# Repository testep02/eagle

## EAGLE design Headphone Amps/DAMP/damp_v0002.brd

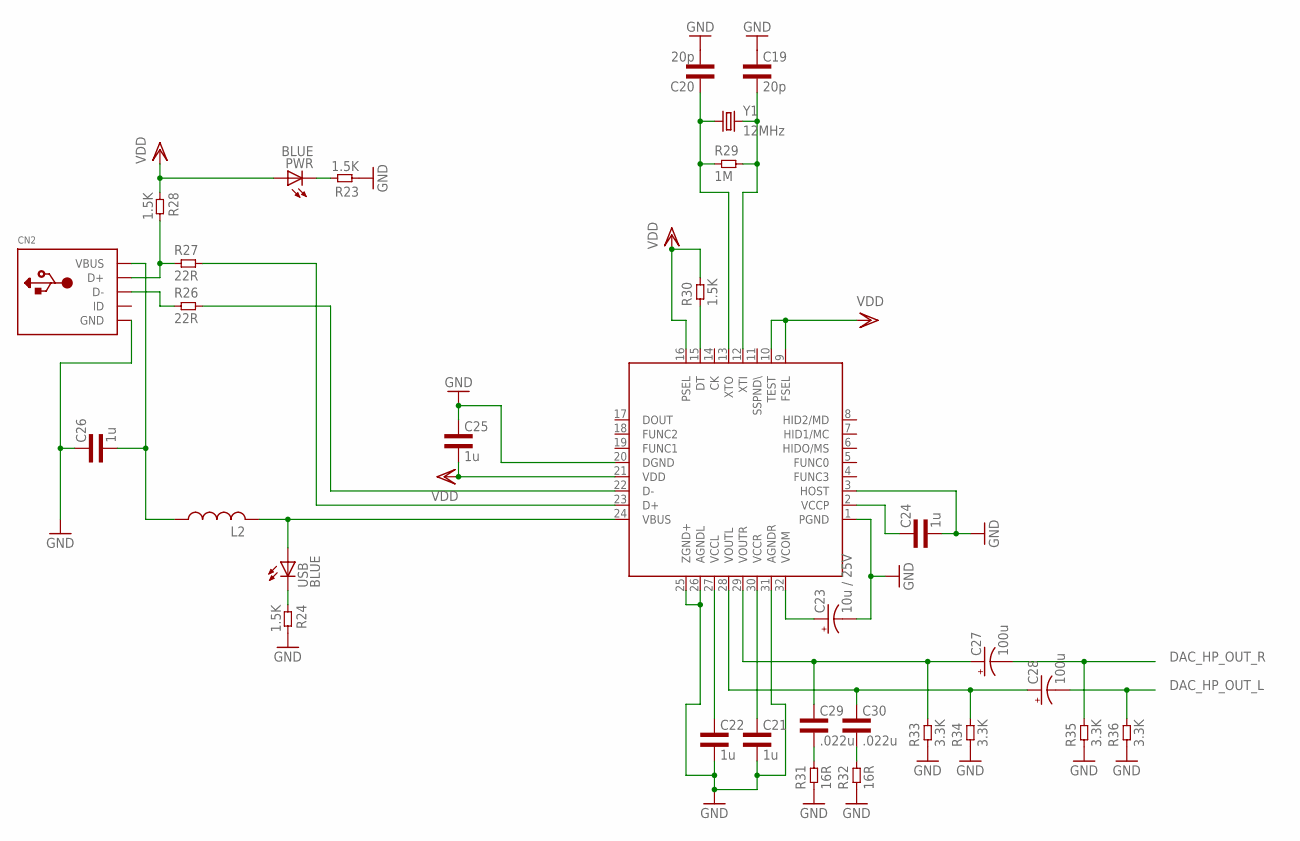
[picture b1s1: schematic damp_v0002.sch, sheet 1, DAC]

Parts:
C19, C20: 20p; 0603L3
C21, C22, C24, C25, C26: 1u; 0603L3
C23: 10u / 25V; E1,8-4
C27, C28: 100u; E2-5
C29, C30: .022u; 0603L3
CN2: USBMINIB; USB-MINIB
L2: RCL_L-USL3225M; RCL_L3225M
PWR: BLUE; LED-0603
R23, R24, R28, R30: 1.5K; 0603L3
R26, R27: 22R; 0603L3
R29: 1M; 0603L3
R31, R32: 16R; 0603L3
R33, R34, R35, R36: 3.3K; 0603L3
U$1: PCM2707_V1_PCM2704C_PCM2707
USB: BLUE; LED-0603
Y1: 12MHz; HC49US

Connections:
DAC_HP_OUT_L: C28.-, R36.P$2 (2); also elsewhere on the board
DAC_HP_OUT_R: C27.-, R35.P$2 (2); also elsewhere on the board
GND: C19.P$1 (1), C20.P$2 (2), C21.P$2 (2), C22.P$2 (2), C23.-, C24.P$2 (2), C25.P$1 (1), C26.P$1 (1), CN2.GND, R23.P$1 (1), R24.P$2 (2), R31.P$1 (1), R32.P$1 (1), R33.P$1 (1), R34.P$1 (1), R35.P$1 (1), R36.P$1 (1), U$1.1 (PGND), U$1.3 (HOST), U$1.20 (DGND), U$1.25 (ZGND+), U$1.26 (AGNDL), U$1.31 (AGNDR); also elsewhere on the board
unnamed: PWR.C, R23.P$2 (2)
unnamed: R24.P$1 (1), USB.C
unnamed: CN2.D+, R27.P$1 (1), R28.P$2 (2)
unnamed: CN2.D-, R26.P$1 (1)
unnamed: R27.P$2 (2), U$1.23 (D+)
unnamed: R26.P$2 (2), U$1.22 (D-)
unnamed: C20.P$1 (1), R29.P$1 (1), U$1.13 (XTO), Y1.1
unnamed: C19.P$2 (2), R29.P$2 (2), U$1.12 (XTI), Y1.2
unnamed: C22.P$1 (1), U$1.27 (VCCL)
unnamed: C21.P$1 (1), U$1.30 (VCCR)
unnamed: C23.+, U$1.32 (VCOM)
unnamed: C29.P$2 (2), R31.P$2 (2)
unnamed: C24.P$1 (1), U$1.2 (VCCP)
unnamed: C27.+, C29.P$1 (1), R33.P$2 (2), U$1.29 (VOUTR)
unnamed: L2.2, U$1.24 (VBUS), USB.A
unnamed: C26.P$2 (2), CN2.VBUS, L2.1
unnamed: C28.+, C30.P$1 (1), R34.P$2 (2), U$1.28 (VOUTL)
unnamed: R30.P$1 (1), U$1.15 (DT)
unnamed: C30.P$2 (2), R32.P$2 (2)
VDD: C25.P$2 (2), PWR.A, R28.P$1 (1), R30.P$2 (2), U$1.9 (FSEL), U$1.10 (TEST), U$1.16 (PSEL), U$1.21 (VDD)

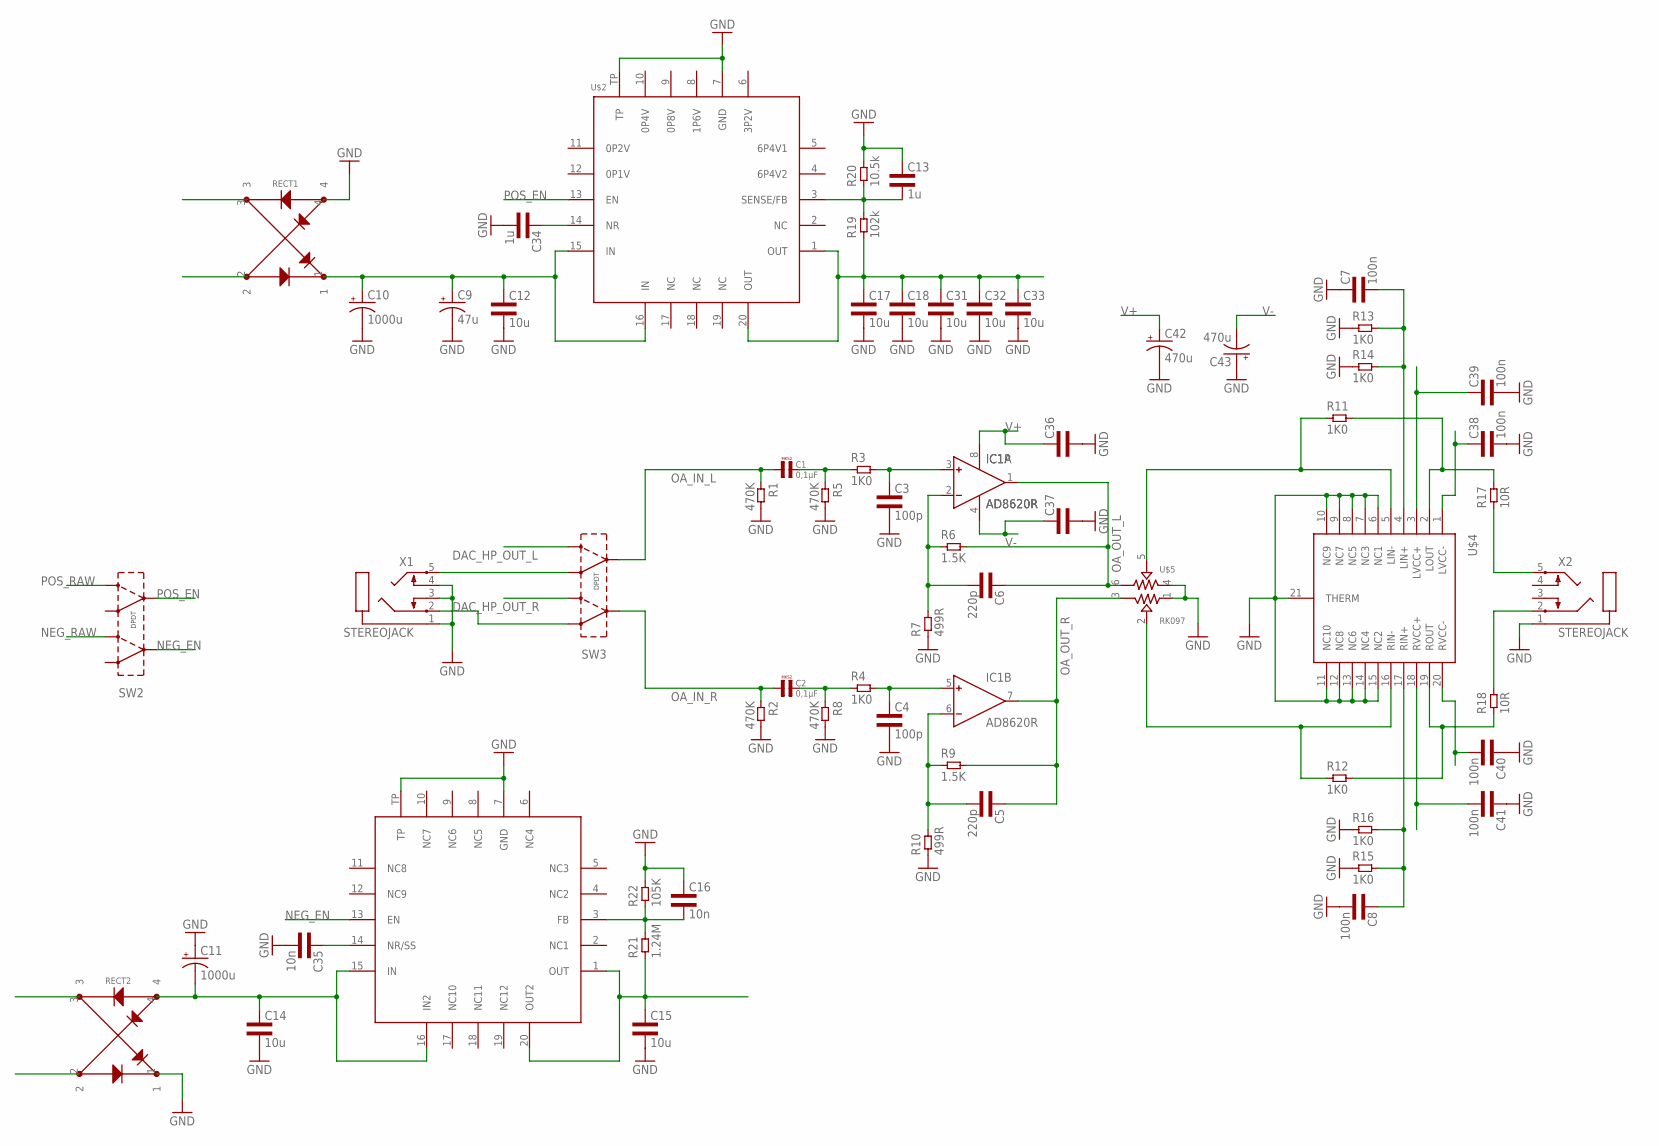
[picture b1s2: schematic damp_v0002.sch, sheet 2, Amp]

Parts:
C1, C2: 0,1µF; R5B2K5
C3, C4: 100p; 0603L3
C5, C6: 220p; 0603L3
C7, C8, C38, C39, C40, C41: 100n; 0603L3
C9: 47u; CT7343
C10, C11: 1000u; E7,5-16
C12, C14, C15, C17, C18, C31, C32, C33: 10u; 0805L3
C13, C34: 1u; 0603L3
C16, C35: 10n; 0603L3
C36, C37: CAP0603L3; 0603L3
C42, C43: 470u; E5-10,5
IC1: AD8620R; SO8
R1, R2, R5, R8: 470K; 0603L3
R3, R4, R11, R12, R13, R14, R15, R16: 1K0; 0603L3
R6, R9: 1.5K; 0603L3
R7, R10: 499R; 0603L3
R17, R18: 10R; 1206L3
R19: 102k; 0603L3
R20: 10.5k; 0603L3
R21: 1.24M; 0603L3
R22: 105K; 0603L3
RECT1, RECT2: RECTIFIER_Z4GP206; RECTIFIER_ABS-4
SW2, SW3: DPDTCAS-A; CAS-A
U$2: POWER-SUPPLY_POS_V1_TI_LDO_TPS7A4700; POWER-SUPPLY_POS_V1_TI_LDO_VQFN-20
U$3: POWER-SUPPLY_POS_V1_TI_LDO_TPS7A3301RGWT; POWER-SUPPLY_POS_V1_TI_LDO_VQFN-20
U$4: PCM2707_V1_AMP_TPA6120_TPA6120
U$5: RK097
X1, X2: STEREOJACK; STX3100

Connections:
AC1: RECT1.3
AC2: RECT1.2
AC3: RECT2.3
AC4: RECT2.2
DAC_HP_OUT_L: SW3.P$6 (OUTB2); also elsewhere on the board
DAC_HP_OUT_R: SW3.P$3 (OUTA2); also elsewhere on the board
GND: C3.P$2 (2), C4.P$2 (2), C7.P$1 (1), C8.P$2 (2), C9.-, C10.-, C11.+, C12.2, C13.P$1 (1), C14.2, C15.2, C16.P$1 (1), C17.2, C18.2, C31.2, C32.2, C33.2, C34.P$2 (2), C35.P$2 (2), C36.P$2 (2), C37.P$2 (2), C38.P$2 (2), C39.P$2 (2), C40.P$1 (1), C41.P$1 (1), C42.-, C43.+, R1.P$2 (2), R2.P$2 (2), R5.P$2 (2), R7.P$1 (1), R8.P$2 (2), R10.P$1 (1), R13.P$1 (1), R14.P$1 (1), R15.P$1 (1), R16.P$1 (1), R20.P$2 (2), R22.P$2 (2), RECT1.4, RECT2.1, U$2.7 (GND), U$2.TP, U$3.7 (GND), U$3.TP, U$4.6 (NC1), U$4.7 (NC3), U$4.8 (NC5), U$4.9 (NC7), U$4.10 (NC9), U$4.11 (NC10), U$4.12 (NC8), U$4.13 (NC6), U$4.14 (NC4), U$4.15 (NC2), U$4.21 (THERM), U$5.1, U$5.4, X1.1, X1.3, X1.4, X2.1; also elsewhere on the board
unnamed: SW3.P$4 (OUTB1), X1.5
unnamed: SW3.P$1 (OUTA1), X1.2
unnamed: C34.P$1 (1), U$2.14 (NR)
unnamed: C1.2, R3.P$1 (1), R5.P$1 (1)
unnamed: C3.P$1 (1), IC1.3 (IN+), R3.P$2 (2)
unnamed: C6.P$2 (2), IC1.2 (IN-), R6.P$1 (1), R7.P$2 (2)
unnamed: R11.P$1 (1), U$4.5 (LIN-), U$5.5
unnamed: R12.P$1 (1), U$4.16 (RIN-), U$5.2
unnamed: C2.2, R4.P$1 (1), R8.P$1 (1)
unnamed: C4.P$1 (1), IC1.5 (IN+), R4.P$2 (2)
unnamed: R11.P$2 (2), R17.2, U$4.2 (LOUT)
unnamed: C5.P$2 (2), IC1.6 (IN-), R9.P$1 (1), R10.P$2 (2)
unnamed: R12.P$2 (2), R18.1, U$4.19 (ROUT)
unnamed: C7.P$2 (2), R13.P$2 (2), R14.P$2 (2), U$4.4 (LIN+)
unnamed: C8.P$1 (1), R15.P$2 (2), R16.P$2 (2), U$4.17 (RIN+)
unnamed: R17.1, X2.5
unnamed: R18.2, X2.2
unnamed: C13.P$2 (2), R19.P$2 (2), R20.P$1 (1), U$2.3 (SENSE/FB)
unnamed: C16.P$2 (2), R21.P$2 (2), R22.P$1 (1), U$3.3 (FB)
unnamed: C35.P$1 (1), U$3.14 (NR/SS)
NEG_EN: SW2.P$2 (INA), U$3.13 (EN)
NEG_RAW: C11.-, C14.1, RECT2.4, SW2.P$3 (OUTA2), U$3.15 (IN), U$3.16 (IN2)
OA_IN_L: C1.1, R1.P$1 (1), SW3.P$5 (INB)
OA_IN_R: C2.1, R2.P$1 (1), SW3.P$2 (INA)
OA_OUT_L: C6.P$1 (1), IC1.1 (OUT), R6.P$2 (2), U$5.6
OA_OUT_R: C5.P$1 (1), IC1.7 (OUT), R9.P$2 (2), U$5.3
POS_EN: SW2.P$5 (INB), U$2.13 (EN)
POS_RAW: C9.+, C10.+, C12.1, RECT1.1, SW2.P$6 (OUTB2), U$2.15 (IN), U$2.16 (IN)
V+: C17.1, C18.1, C31.1, C32.1, C33.1, C36.P$1 (1), C39.P$1 (1), C41.P$2 (2), C42.+, IC1.8 (V+), R19.P$1 (1), U$2.1 (OUT), U$2.20 (OUT), U$4.3 (LVCC+), U$4.18 (RVCC+)
V-: C15.1, C37.P$1 (1), C38.P$1 (1), C40.P$2 (2), C43.-, IC1.4 (V-), R21.P$1 (1), U$3.1 (OUT), U$3.20 (OUT2), U$4.1 (LVCC-), U$4.20 (RVCC-)

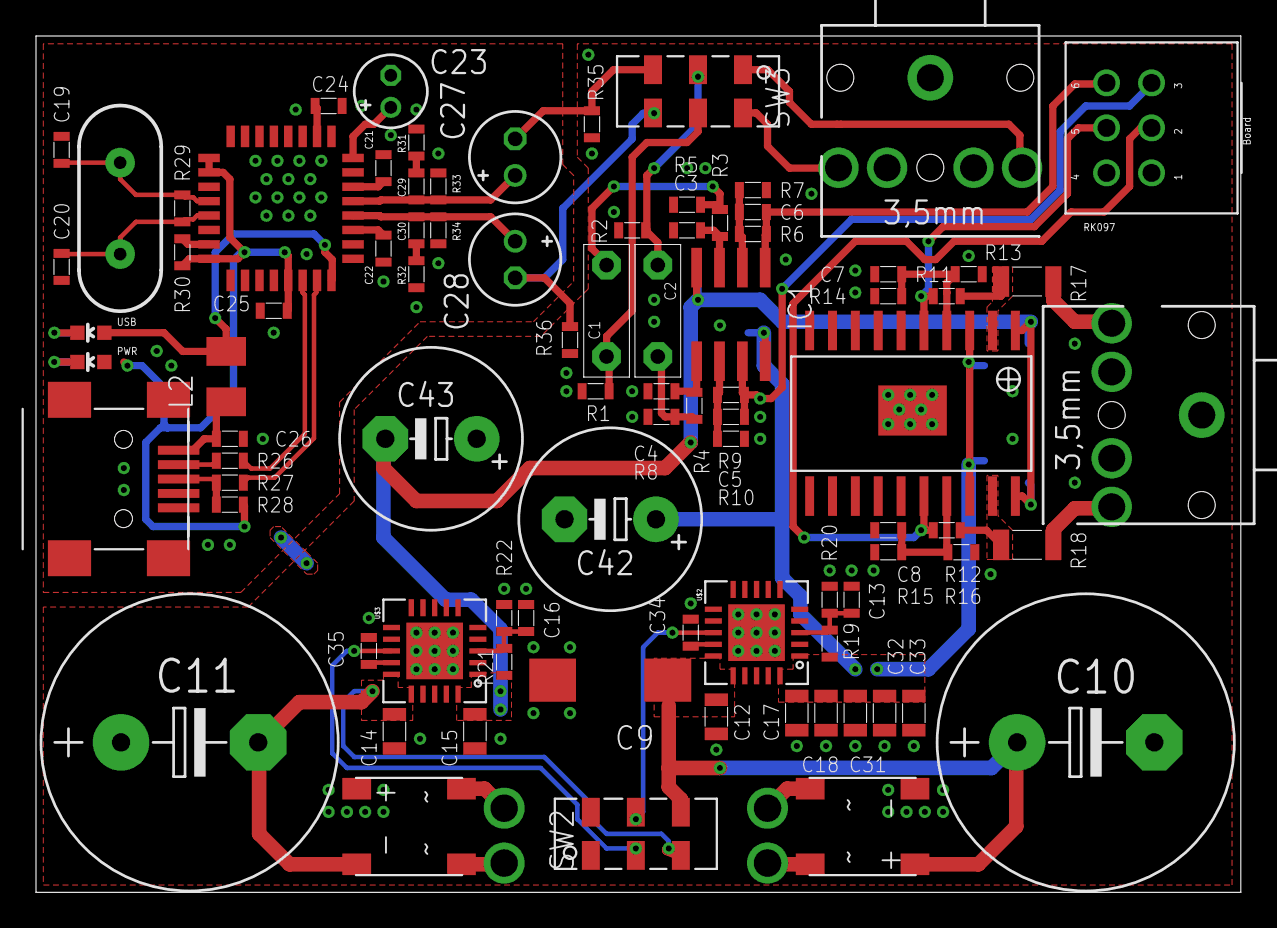
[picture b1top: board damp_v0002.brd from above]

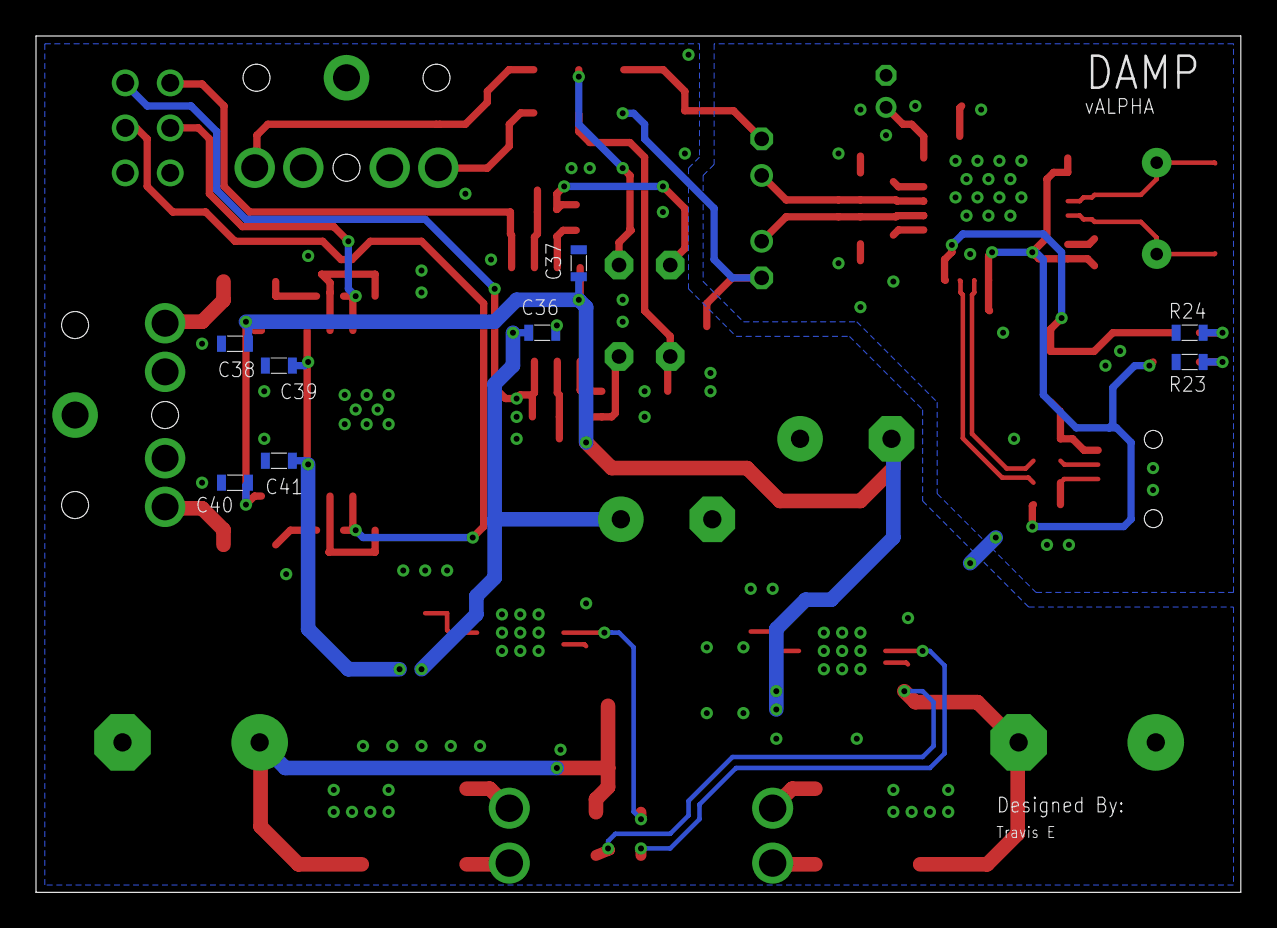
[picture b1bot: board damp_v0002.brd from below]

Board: 2 copper layers, 66.9 x 47.6 mm, 95 parts (8 on the bottom side), 53 nets.

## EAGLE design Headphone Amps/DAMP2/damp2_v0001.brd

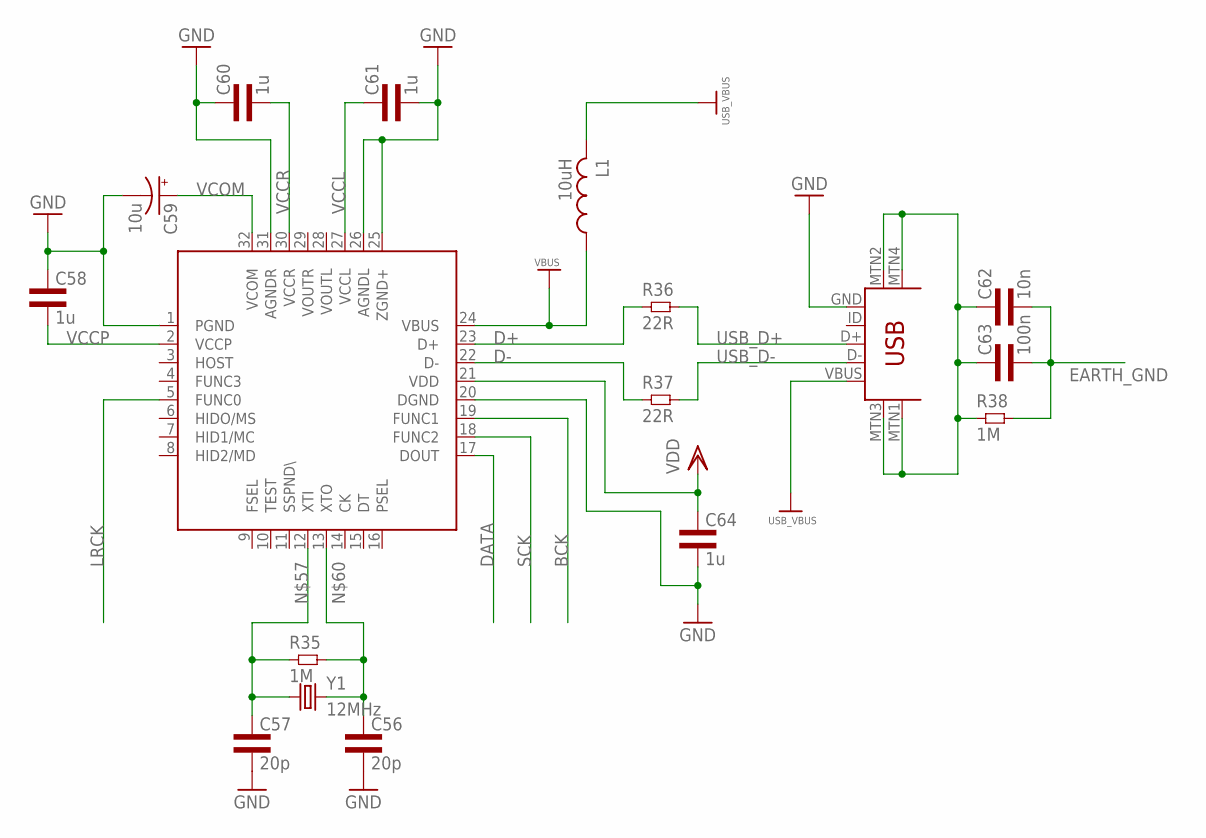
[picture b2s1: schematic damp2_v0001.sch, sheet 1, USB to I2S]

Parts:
C56, C57: 20p; 0603L3
C58, C60, C61, C64: 1u; 0603L3
C59: 10u; E1,8-4
C62: 10n; 0603L3
C63: 100n; 0603L3
L1: 10uH; L3225M
R35, R38: 1M; 0603L3
R36, R37: 22R; 0603L3
U$1: PCM2707_V1_PCM2704C_PCM2707
U$9: USB-MINIB-5PIN; USB-MINIB
Y1: 12MHz; HC49US

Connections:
BCK: U$1.19 (FUNC1); also elsewhere on the board
D+: R36.P$1 (1), U$1.23 (D+)
D-: R37.P$1 (1), U$1.22 (D-)
DATA: U$1.17 (DOUT); also elsewhere on the board
EARTH_GND: C62.P$2 (2), C63.P$2 (2), R38.P$2 (2)
GND: C56.P$2 (2), C57.P$2 (2), C58.P$1 (1), C59.-, C60.P$1 (1), C61.P$2 (2), C64.P$2 (2), U$1.1 (PGND), U$1.20 (DGND), U$1.25 (ZGND+), U$1.26 (AGNDL), U$1.31 (AGNDR), U$9.GND; also elsewhere on the board
LRCK: U$1.5 (FUNC0); also elsewhere on the board
unnamed: C57.P$1 (1), R35.P$1 (1), U$1.12 (XTI), Y1.1
unnamed: C56.P$1 (1), R35.P$2 (2), U$1.13 (XTO), Y1.2
unnamed: C62.P$1 (1), C63.P$1 (1), R38.P$1 (1), U$9.MTN1 (MTN2), U$9.MTN2 (MTN3), U$9.MTN3 (MTN1), U$9.MTN4
SCK: U$1.18 (FUNC2); also elsewhere on the board
USB_D+: R36.P$2 (2), U$9.D+
USB_D-: R37.P$2 (2), U$9.D-
USB_VBUS: L1.2, U$9.VBUS
VBUS: L1.1, U$1.24 (VBUS)
VCCL: C61.P$1 (1), U$1.27 (VCCL)
VCCP: C58.P$2 (2), U$1.2 (VCCP)
VCCR: C60.P$2 (2), U$1.30 (VCCR)
VCOM: C59.+, U$1.32 (VCOM)
VDD: C64.P$1 (1), U$1.21 (VDD)

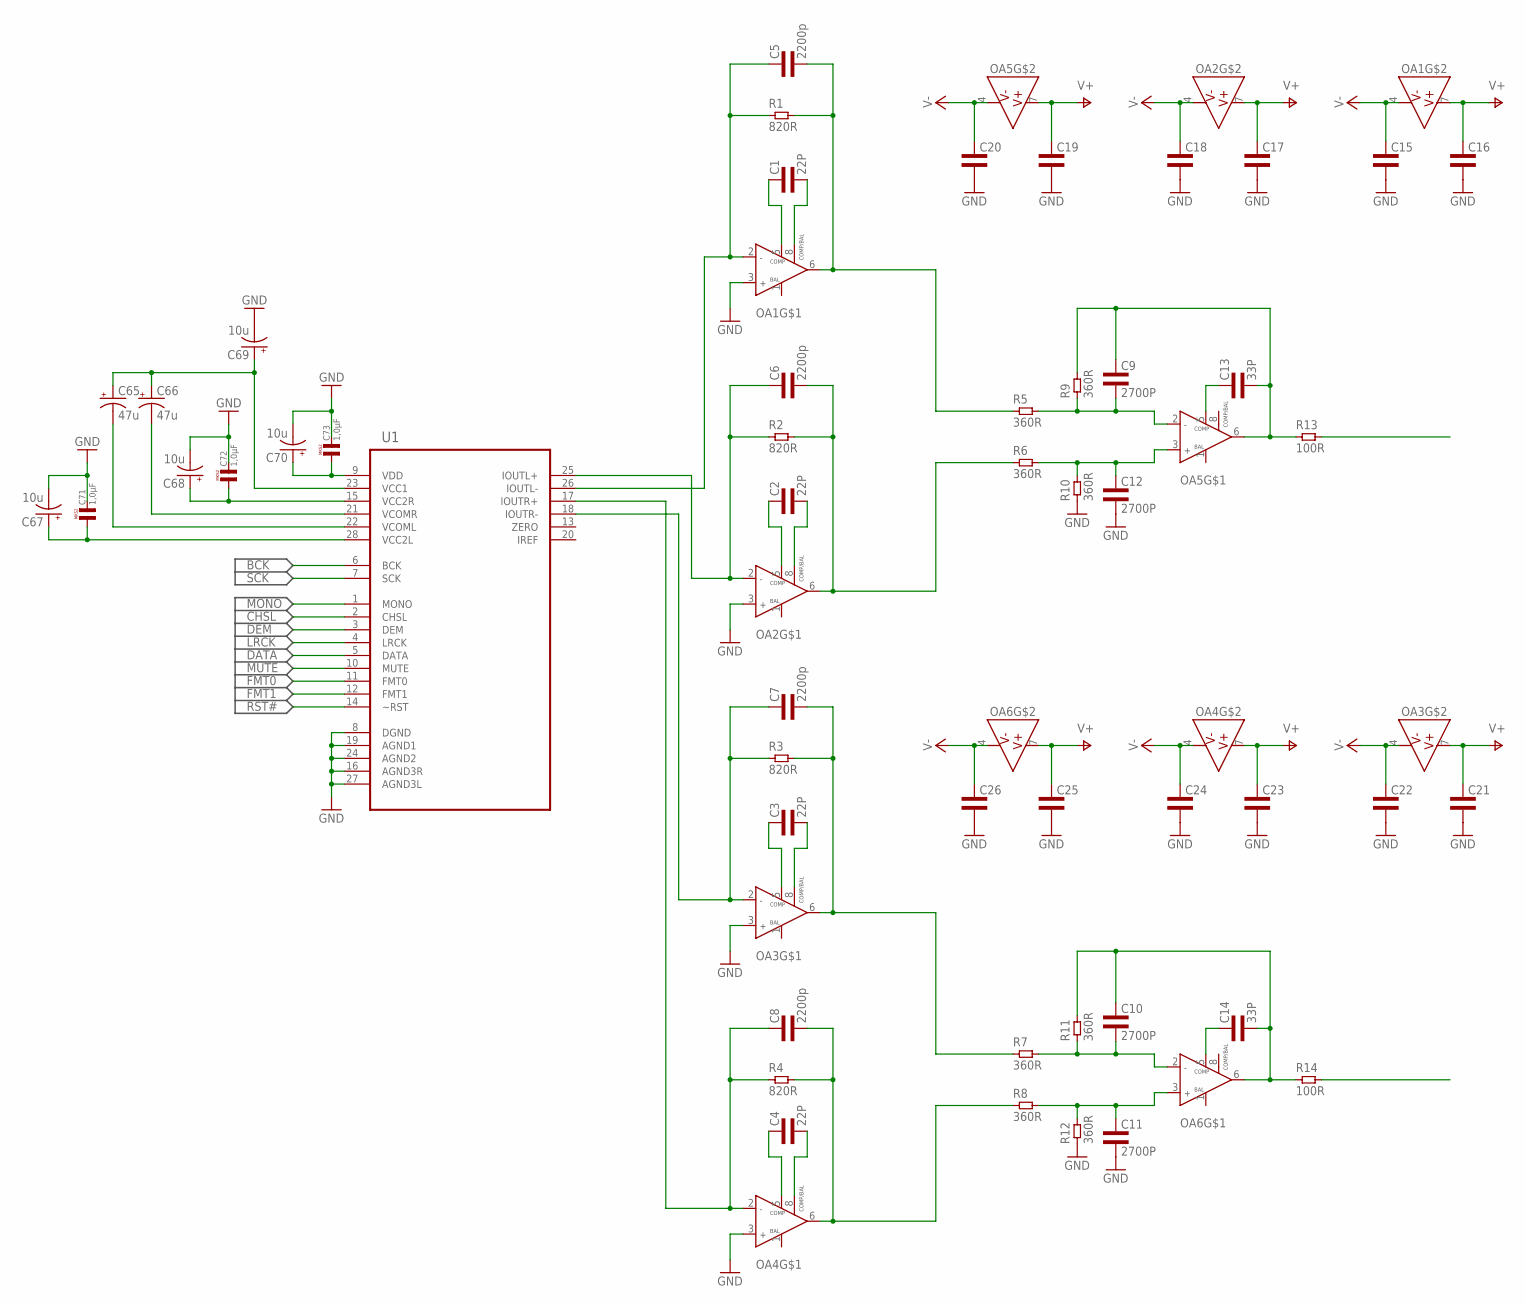
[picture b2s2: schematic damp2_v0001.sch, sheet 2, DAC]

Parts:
C1, C2, C3, C4: 22P; 0603L3
C5, C6, C7, C8: 2200p; 0603L3
C9, C10, C11, C12: 2700P; 0805L3
C13, C14: 33P; 0603L3
C15, C16, C17, C18, C19, C20, C21, C22, C23, C24, C25, C26: CAP0603L3; 0603L3
C65, C66: 47u; A/3216-18W
C67, C68, C69, C70: 10u; A/3216-18W
C71, C72, C73: 1,0µF; R5B5
OA1, OA2, OA3, OA4: NE5534DSOIC8; SOIC-8
OA5, OA6: NE5534ADSOIC8; SOIC-8
R1, R2, R3, R4: 820R; 0603L3
R5, R6, R7, R8, R9, R10, R11, R12: 360R; 0805L3
R13, R14: 100R; 0805L3
U1: TEXAS-INSTRUMENTS_BY_ELEMENT14_BATCH_1_PCM1794ADB; TEXAS-INSTRUMENTS_BY_ELEMENT14_BATCH_1_SOP65P780X200-28N

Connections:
BCK: U1.6 (BCK); also elsewhere on the board
CHSL: U1.2 (CHSL)
DATA: U1.5 (DATA); also elsewhere on the board
DEM: U1.3 (DEM)
FMT0: U1.11 (FMT0)
FMT1: U1.12 (FMT1)
GND: C11.2, C12.2, C15.P$2 (2), C16.P$2 (2), C17.P$2 (2), C18.P$2 (2), C19.P$2 (2), C20.P$2 (2), C21.P$2 (2), C22.P$2 (2), C23.P$2 (2), C24.P$2 (2), C25.P$2 (2), C26.P$2 (2), C67.-, C68.-, C69.-, C70.-, C71.2, C72.2, C73.2, OA1.3 (IN+), OA2.3 (IN+), OA3.3 (IN+), OA4.3 (IN+), R10.1, R12.1, U1.8 (DGND), U1.16 (AGND3R), U1.19 (AGND1), U1.24 (AGND2), U1.27 (AGND3L); also elsewhere on the board
LRCK: U1.4 (LRCK); also elsewhere on the board
MONO: U1.1 (MONO)
MUTE: U1.10 (MUTE)
unnamed: C1.P$1 (1), OA1.5 (COMP)
unnamed: C1.P$2 (2), OA1.8 (COMP/BAL)
unnamed: C2.P$1 (1), OA2.5 (COMP)
unnamed: C2.P$2 (2), OA2.8 (COMP/BAL)
unnamed: C3.P$1 (1), OA3.5 (COMP)
unnamed: C3.P$2 (2), OA3.8 (COMP/BAL)
unnamed: C4.P$1 (1), OA4.5 (COMP)
unnamed: C4.P$2 (2), OA4.8 (COMP/BAL)
unnamed: C5.P$1 (1), OA1.2 (IN-), R1.P$1 (1), U1.26 (IOUTL-)
unnamed: C6.P$1 (1), OA2.2 (IN-), R2.P$1 (1), U1.25 (IOUTL+)
unnamed: C7.P$1 (1), OA3.2 (IN-), R3.P$1 (1), U1.18 (IOUTR-)
unnamed: C8.P$1 (1), OA4.2 (IN-), R4.P$1 (1), U1.17 (IOUTR+)
unnamed: C6.P$2 (2), OA2.6 (OUT), R2.P$2 (2), R6.1
unnamed: C5.P$2 (2), OA1.6 (OUT), R1.P$2 (2), R5.1
unnamed: C7.P$2 (2), OA3.6 (OUT), R3.P$2 (2), R7.1
unnamed: C8.P$2 (2), OA4.6 (OUT), R4.P$2 (2), R8.1
unnamed: C10.2, OA6.2 (IN-), R7.2, R11.1
unnamed: C11.1, OA6.3 (IN+), R8.2, R12.2
unnamed: C9.2, OA5.2 (IN-), R5.2, R9.1
unnamed: C12.1, OA5.3 (IN+), R6.2, R10.2
unnamed: C13.P$1 (1), OA5.5 (COMP)
unnamed: C14.P$1 (1), OA6.5 (COMP)
unnamed: C10.1, C14.P$2 (2), OA6.6 (OUT), R11.2, R14.1
unnamed: C9.1, C13.P$2 (2), OA5.6 (OUT), R9.2, R13.1
unnamed: C70.+, C73.1, U1.9 (VDD)
unnamed: C65.+, C66.+, C69.+, U1.23 (VCC1)
unnamed: C68.+, C72.1, U1.15 (VCC2R)
unnamed: C66.-, U1.21 (VCOMR)
unnamed: C65.-, U1.22 (VCOML)
unnamed: C67.+, C71.1, U1.28 (VCC2L)
RST#: U1.14 (~RST)
SCK: U1.7 (SCK); also elsewhere on the board
V+: C16.P$1 (1), C17.P$1 (1), C19.P$1 (1), C21.P$1 (1), C23.P$1 (1), C25.P$1 (1), OA1.7 (V+), OA2.7 (V+), OA3.7 (V+), OA4.7 (V+), OA5.7 (V+), OA6.7 (V+); also elsewhere on the board
V-: C15.P$1 (1), C18.P$1 (1), C20.P$1 (1), C22.P$1 (1), C24.P$1 (1), C26.P$1 (1), OA1.4 (V-), OA2.4 (V-), OA3.4 (V-), OA4.4 (V-), OA5.4 (V-), OA6.4 (V-); also elsewhere on the board

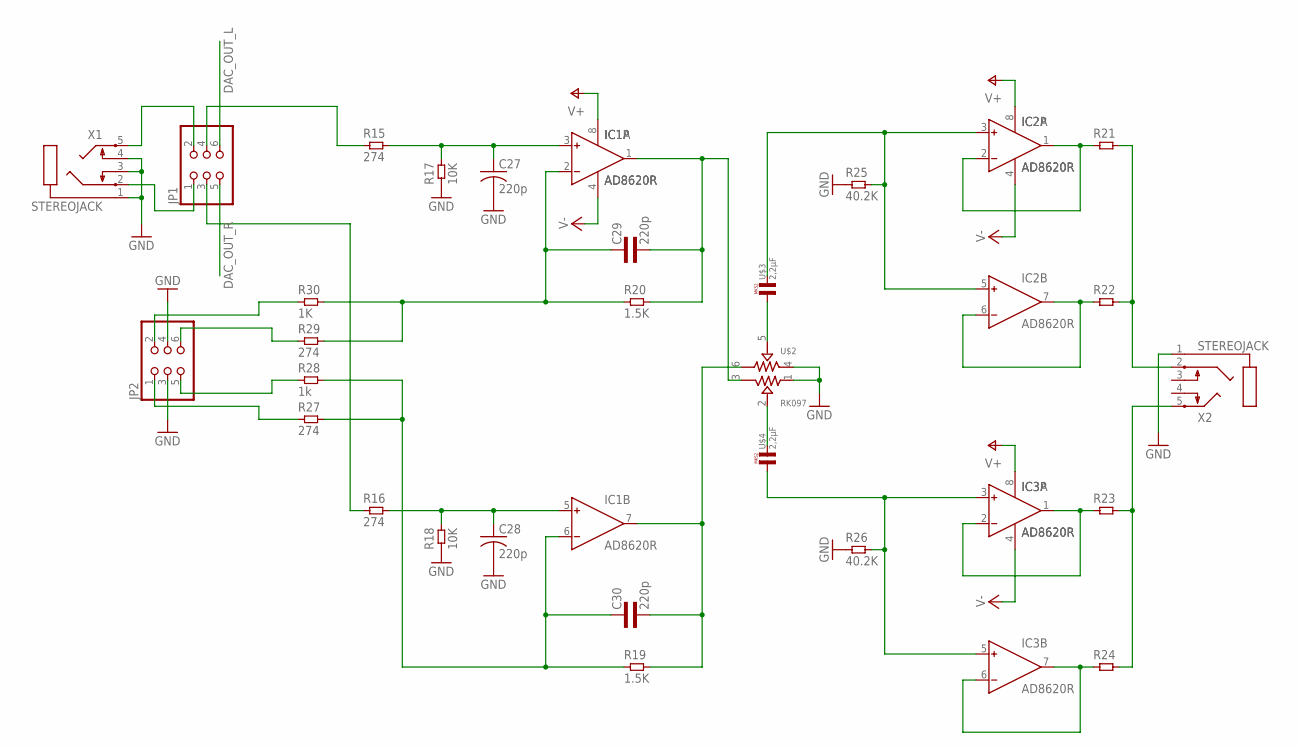
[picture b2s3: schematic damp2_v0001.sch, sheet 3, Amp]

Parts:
C27, C28: 220p; C025-025X050
C29, C30: 220p; 0805L3
IC1, IC2, IC3: AD8620R; SO8
JP1, JP2: PINHD-2X3; 2X03
R15, R16, R27, R29: 274; 0805L3
R17, R18: 10K; 0805L3
R19, R20: 1.5K; 0805L3
R21, R22, R23, R24: RES1206L3; 1206L3
R25, R26: 40.2K; 0805L3
R28: 1k; 0805L3
R30: 1K; 0805L3
U$2: RK097
U$3, U$4: 2,2µF; R5B7K2
X1, X2: STEREOJACK; STX3100

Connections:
AMP_IN_L: JP1.4, R15.1
AMP_IN_R: JP1.3, R16.1
A_IN_L: JP1.2, X1.5
A_IN_R: JP1.1, X1.2
DAC_OUT_L: JP1.6
DAC_OUT_R: JP1.5
GND: C27.2, C28.2, JP2.3, JP2.4, R17.1, R18.1, R25.1, R26.1, U$2.1, U$2.4, X1.1, X1.3, X1.4, X2.1; also elsewhere on the board
unnamed: C27.1, IC1.3 (IN+), R15.2, R17.2
unnamed: C28.1, IC1.5 (IN+), R16.2, R18.2
unnamed: C29.2, IC1.1 (OUT), R20.2, U$2.3
unnamed: C30.2, IC1.7 (OUT), R19.2, U$2.6
unnamed: C30.1, IC1.6 (IN-), R19.1, R27.2, R28.2
unnamed: C29.1, IC1.2 (IN-), R20.1, R29.2, R30.2
unnamed: U$2.2, U$4.2
unnamed: IC2.1 (OUT), IC2.2 (IN-), R21.1
unnamed: IC2.6 (IN-), IC2.7 (OUT), R22.1
unnamed: IC3.1 (OUT), IC3.2 (IN-), R23.1
unnamed: IC3.6 (IN-), IC3.7 (OUT), R24.1
unnamed: R21.2, R22.2, X2.2
unnamed: R23.2, R24.2, X2.5
unnamed: U$2.5, U$3.1
unnamed: IC3.3 (IN+), IC3.5 (IN+), R26.2, U$4.1
unnamed: IC2.3 (IN+), IC2.5 (IN+), R25.2, U$3.2
unnamed: JP2.2, R30.1
unnamed: JP2.1, R27.1
unnamed: JP2.5, R28.1
unnamed: JP2.6, R29.1
V+: IC1.8 (V+), IC2.8 (V+), IC3.8 (V+); also elsewhere on the board
V-: IC1.4 (V-), IC2.4 (V-), IC3.4 (V-); also elsewhere on the board

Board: 2 copper layers, 103 parts (2 on the bottom side), 76 nets, no tracks yet.

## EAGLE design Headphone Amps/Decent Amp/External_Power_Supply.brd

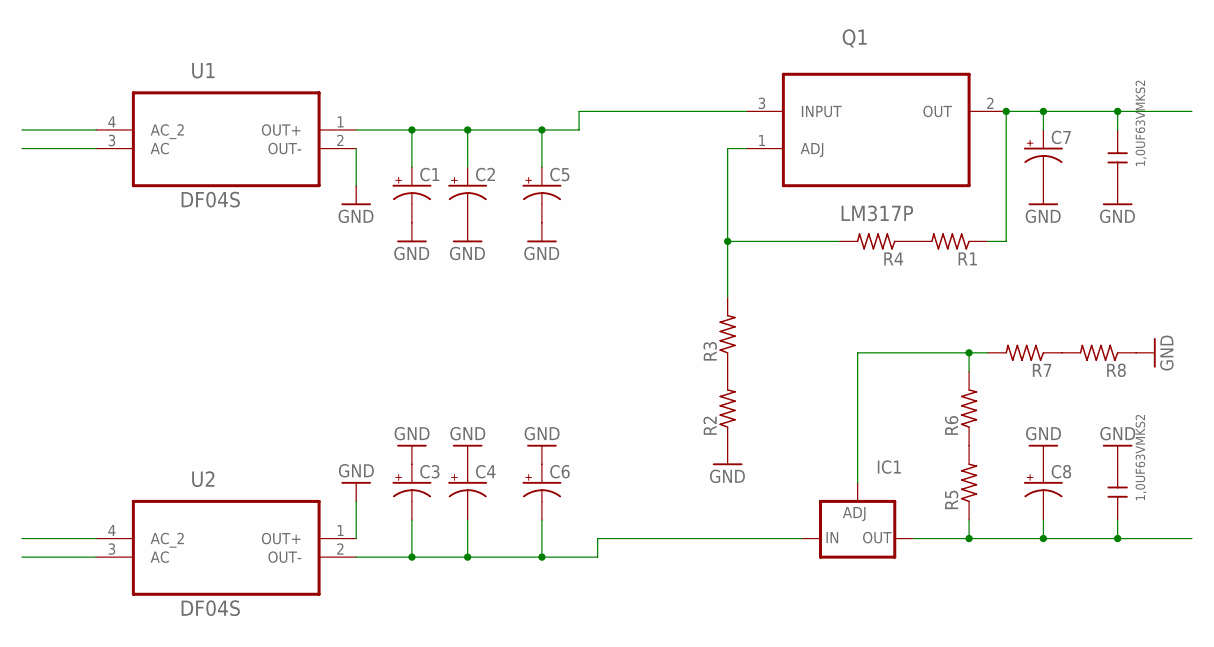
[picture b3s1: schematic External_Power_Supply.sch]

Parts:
C1, C2, C3, C4: CPOL-US153CLV-1010; 153CLV-1010
C5, C6, C7, C8: CPOL-USF; PANASONIC_F
C9, C10: 1,0UF63VMKS2; 5,0X10,0RM5,0
IC1: LM337TS; 337TS
Q1: LM317P; TO254P450X1020X2000-3P
R1, R2, R3, R4, R5, R6, R7, R8: R-US_R0603; R0603
U1, U2: DF04S; SOT508P985X260-4N

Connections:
GND: C1.-, C2.-, C3.+, C4.+, C5.-, C6.+, C7.-, C8.+, C9.1, C10.2, R2.1, R8.1, U1.2 (OUT-), U2.1 (OUT+)
unnamed: R2.2, R3.1
unnamed: C1.+, C2.+, C5.+, Q1.3 (INPUT), U1.1 (OUT+)
unnamed: C3.-, C4.-, C6.-, IC1.2 (IN), U2.2 (OUT-)
unnamed: C7.+, C9.2, Q1.2 (OUT), R1.1
unnamed: C8.-, C10.1, IC1.3 (OUT), R5.1
unnamed: Q1.1 (ADJ), R3.2, R4.2
unnamed: IC1.1 (ADJ), R6.2, R7.2
unnamed: R1.2, R4.1
unnamed: R5.2, R6.1
unnamed: R7.1, R8.2

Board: 2 copper layers, 22 parts (0 on the bottom side), 11 nets, no tracks yet.

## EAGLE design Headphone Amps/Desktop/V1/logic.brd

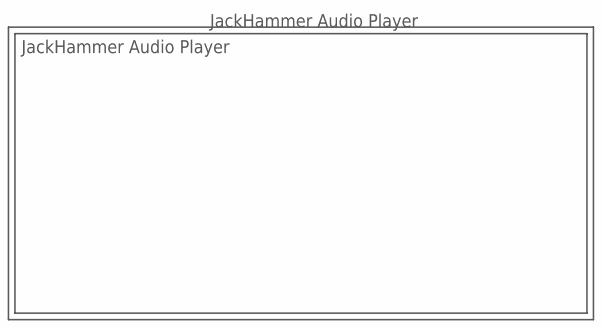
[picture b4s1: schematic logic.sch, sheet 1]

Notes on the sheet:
JackHammer Audio Player

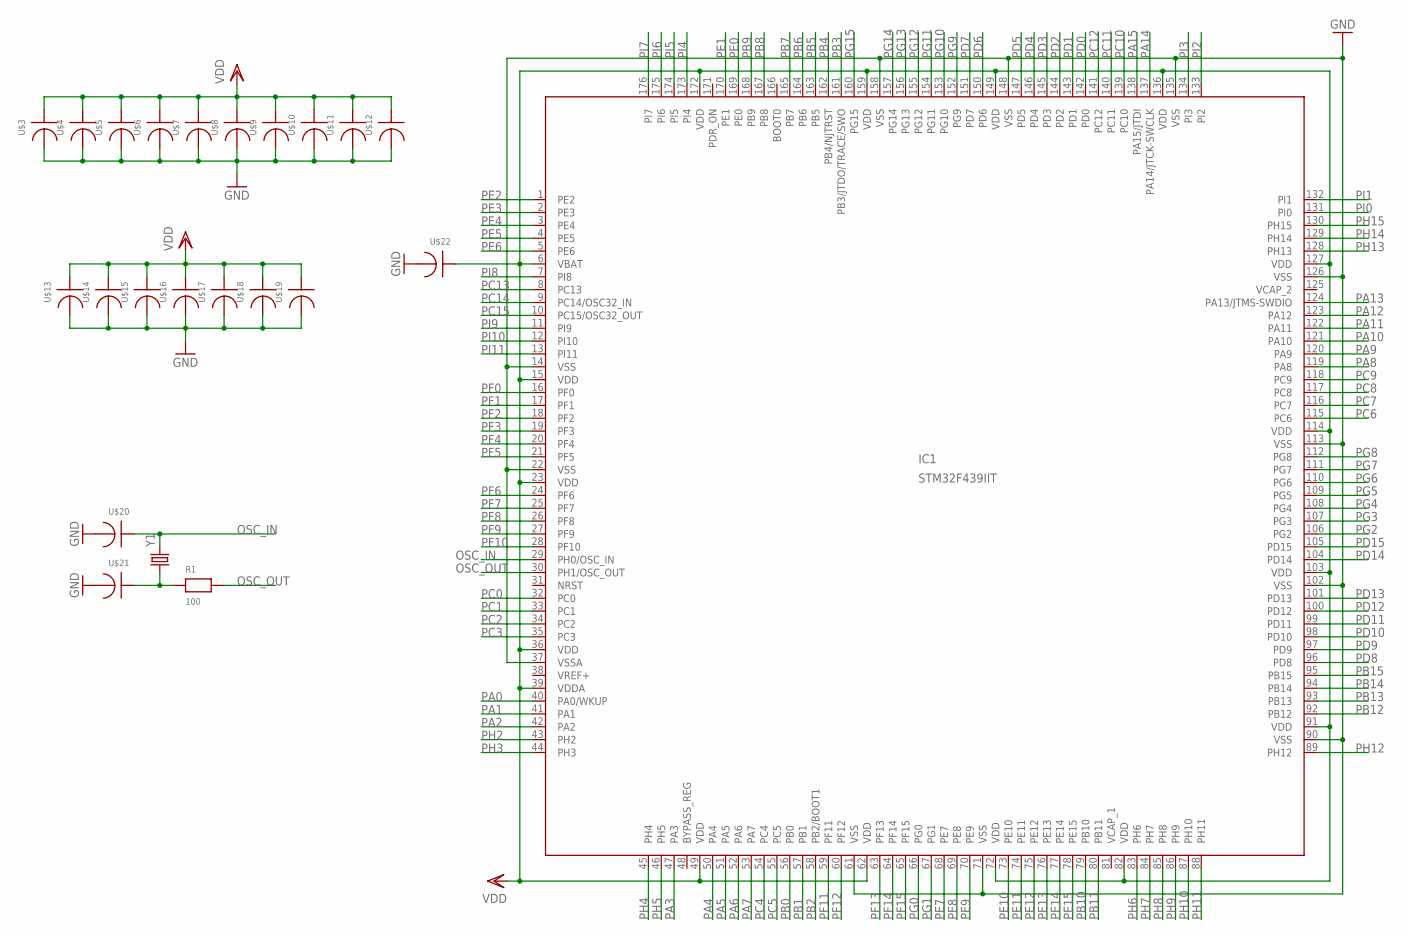
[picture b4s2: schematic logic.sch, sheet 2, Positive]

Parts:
IC1: STM32F439IIT; LQFP-176
R1: 100; R0402
U$3, U$4, U$5, U$6, U$7, U$8, U$9, U$10, U$11, U$12, U$13, U$14, U$15, U$16, U$17, U$18, U$19, U$20, U$21, U$22: PCAP0402LEVEL3; R0402
Y1: CRYSTALHC49US; HC49US

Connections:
GND: IC1.14 (VSS), IC1.22 (VSS), IC1.37 (VSSA), IC1.61 (VSS), IC1.71 (VSS), IC1.90 (VSS), IC1.102 (VSS), IC1.113 (VSS), IC1.126 (VSS), IC1.135 (VSS), IC1.148 (VSS), IC1.158 (VSS), U$3.P$1, U$4.P$1, U$5.P$1, U$6.P$1, U$7.P$1, U$8.P$1, U$9.P$1, U$10.P$1, U$11.P$1, U$12.P$1, U$13.P$1, U$14.P$1, U$15.P$1, U$16.P$1, U$17.P$1, U$18.P$1, U$19.P$1, U$20.P$1, U$21.P$1, U$22.P$1; also elsewhere on the board
unnamed: R1.P$1, U$21.P$2, Y1.1
OSC_IN: IC1.29 (PH0/OSC_IN), U$20.P$2, Y1.2
OSC_OUT: IC1.30 (PH1/OSC_OUT), R1.P$2
PA0: IC1.40 (PA0/WKUP)
PA1: IC1.41 (PA1)
PA2: IC1.42 (PA2)
PA3: IC1.47 (PA3)
PA4: IC1.50 (PA4)
PA5: IC1.51 (PA5)
PA6: IC1.52 (PA6)
PA7: IC1.53 (PA7)
PA8: IC1.119 (PA8)
PA9: IC1.120 (PA9)
PA10: IC1.121 (PA10)
PA11: IC1.122 (PA11)
PA12: IC1.123 (PA12)
PA13: IC1.124 (PA13/JTMS-SWDIO)
PA14: IC1.137 (PA14/JTCK-SWCLK)
PA15: IC1.138 (PA15/JTDI)
PB0: IC1.56 (PB0)
PB1: IC1.57 (PB1)
PB2: IC1.58 (PB2/BOOT1); also elsewhere on the board
PB3: IC1.161 (PB3/JTDO/TRACE/SWO)
PB4: IC1.162 (PB4/NJTRST)
PB5: IC1.163 (PB5); also elsewhere on the board
PB6: IC1.164 (PB6); also elsewhere on the board
PB7: IC1.165 (PB7)
PB8: IC1.167 (PB8); also elsewhere on the board
PB9: IC1.168 (PB9); also elsewhere on the board
PB10: IC1.79 (PB10); also elsewhere on the board
PB11: IC1.80 (PB11)
PB12: IC1.92 (PB12)
PB13: IC1.93 (PB13)
PB14: IC1.94 (PB14); also elsewhere on the board
PB15: IC1.95 (PB15); also elsewhere on the board
PC0: IC1.32 (PC0); also elsewhere on the board
PC1: IC1.33 (PC1)
PC2: IC1.34 (PC2)
PC3: IC1.35 (PC3)
PC4: IC1.54 (PC4)
PC5: IC1.55 (PC5)
PC6: IC1.115 (PC6); also elsewhere on the board
PC7: IC1.116 (PC7); also elsewhere on the board
PC8: IC1.117 (PC8); also elsewhere on the board
PC9: IC1.118 (PC9); also elsewhere on the board
PC10: IC1.139 (PC10); also elsewhere on the board
PC11: IC1.140 (PC11); also elsewhere on the board
PC12: IC1.141 (PC12); also elsewhere on the board
PC13: IC1.8 (PC13); also elsewhere on the board
PC14: IC1.9 (PC14/OSC32_IN); also elsewhere on the board
PC15: IC1.10 (PC15/OSC32_OUT); also elsewhere on the board
PD0: IC1.142 (PD0); also elsewhere on the board
PD1: IC1.143 (PD1); also elsewhere on the board
PD2: IC1.144 (PD2); also elsewhere on the board
PD3: IC1.145 (PD3)
PD4: IC1.146 (PD4)
PD5: IC1.147 (PD5)
PD6: IC1.150 (PD6)
PD7: IC1.151 (PD7)
PD8: IC1.96 (PD8); also elsewhere on the board
PD9: IC1.97 (PD9); also elsewhere on the board
PD10: IC1.98 (PD10); also elsewhere on the board
PD11: IC1.99 (PD11)
PD12: IC1.100 (PD12)
PD13: IC1.101 (PD13)
PD14: IC1.104 (PD14); also elsewhere on the board
PD15: IC1.105 (PD15); also elsewhere on the board
PDR_ON: IC1.171 (PDR_ON)
PE0: IC1.169 (PE0); also elsewhere on the board
PE1: IC1.170 (PE1); also elsewhere on the board
PE2: IC1.1 (PE2)
PE3: IC1.2 (PE3)
PE4: IC1.3 (PE4)
PE5: IC1.4 (PE5)
PE6: IC1.5 (PE6)
PE7: IC1.68 (PE7); also elsewhere on the board
PE8: IC1.69 (PE8); also elsewhere on the board
PE9: IC1.70 (PE9); also elsewhere on the board
PE10: IC1.73 (PE10); also elsewhere on the board
PE11: IC1.74 (PE11); also elsewhere on the board
PE12: IC1.75 (PE12); also elsewhere on the board
PE13: IC1.76 (PE13); also elsewhere on the board
PE14: IC1.77 (PE14); also elsewhere on the board
PE15: IC1.78 (PE15); also elsewhere on the board
PF0: IC1.16 (PF0); also elsewhere on the board
PF1: IC1.17 (PF1); also elsewhere on the board
PF2: IC1.18 (PF2); also elsewhere on the board
PF3: IC1.19 (PF3); also elsewhere on the board
PF4: IC1.20 (PF4); also elsewhere on the board
PF5: IC1.21 (PF5); also elsewhere on the board
PF6: IC1.24 (PF6)
PF7: IC1.25 (PF7)
PF8: IC1.26 (PF8)
PF9: IC1.27 (PF9)
PF10: IC1.28 (PF10)
PF11: IC1.59 (PF11); also elsewhere on the board
PF12: IC1.60 (PF12); also elsewhere on the board
PF13: IC1.63 (PF13); also elsewhere on the board
PF14: IC1.64 (PF14); also elsewhere on the board
PF15: IC1.65 (PF15); also elsewhere on the board
PG0: IC1.66 (PG0); also elsewhere on the board
PG1: IC1.67 (PG1); also elsewhere on the board
PG2: IC1.106 (PG2)
PG3: IC1.107 (PG3)
PG4: IC1.108 (PG4); also elsewhere on the board
PG5: IC1.109 (PG5); also elsewhere on the board
PG6: IC1.110 (PG6)
PG7: IC1.111 (PG7)
PG8: IC1.112 (PG8); also elsewhere on the board
PG9: IC1.152 (PG9)
PG10: IC1.153 (PG10)
PG11: IC1.154 (PG11)
PG12: IC1.155 (PG12)
PG13: IC1.156 (PG13)
PG14: IC1.157 (PG14)
PG15: IC1.160 (PG15); also elsewhere on the board
PH2: IC1.43 (PH2)
PH3: IC1.44 (PH3)
PH4: IC1.45 (PH4)
PH5: IC1.46 (PH5)
PH6: IC1.83 (PH6)
PH7: IC1.84 (PH7)
PH8: IC1.85 (PH8)
PH9: IC1.86 (PH9)
PH10: IC1.87 (PH10)
PH11: IC1.88 (PH11)
PH12: IC1.89 (PH12)
PH13: IC1.128 (PH13)
PH14: IC1.129 (PH14)
PH15: IC1.130 (PH15)
PI0: IC1.131 (PI0)
PI1: IC1.132 (PI1)
PI2: IC1.133 (PI2)
PI3: IC1.134 (PI3)
PI4: IC1.173 (PI4)
PI5: IC1.174 (PI5)
PI6: IC1.175 (PI6)
PI7: IC1.176 (PI7)
PI8: IC1.7 (PI8)
PI9: IC1.11 (PI9)
PI10: IC1.12 (PI10)
PI11: IC1.13 (PI11)
VCAP_1: IC1.81 (VCAP_1)
VCAP_2: IC1.125 (VCAP_2)
VDD: IC1.6 (VBAT), IC1.15 (VDD), IC1.23 (VDD), IC1.36 (VDD), IC1.39 (VDDA), IC1.49 (VDD), IC1.62 (VDD), IC1.72 (VDD), IC1.82 (VDD), IC1.91 (VDD), IC1.103 (VDD), IC1.114 (VDD), IC1.127 (VDD), IC1.136 (VDD), IC1.149 (VDD), IC1.159 (VDD), IC1.172 (VDD), U$3.P$2, U$4.P$2, U$5.P$2, U$6.P$2, U$7.P$2, U$8.P$2, U$9.P$2, U$10.P$2, U$11.P$2, U$12.P$2, U$13.P$2, U$14.P$2, U$15.P$2, U$16.P$2, U$17.P$2, U$18.P$2, U$19.P$2, U$22.P$2; also elsewhere on the board
VREF+: IC1.38 (VREF+)

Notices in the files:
parts and their libraries:
SparkFun-FreqCtrl: Licensing: CC
SparkFun-Electromechanical: Licensing: CC v3.0 Share-Alike You are
SparkFun-Aesthetics: Licensing: CC v3.0 Share-Alike You are welcome to use this library for commercial purposes.
